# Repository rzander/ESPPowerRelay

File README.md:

# DIY - Smart Home Power Relay (ESP8266)
There exists many Relay-Modules based on ESP8266 or other wireless Modules, but I could not find a Module that fits in a european Wallbox and is independent of protocols or wireless standards. That’s why I've created my own Solution: <br>
<br> 

> **Caution: These modules do not have any certifications… In most countries it’s not legal to use it in Production. <br>And: 230V AC can kill !**

The main goals for this Project are:
 -	As **small** as possible
 -	As **cheap** as possible
 -	As **save** as possible
 -	As **flexible** as possible

Specially the flexibility is something important for me, as I have different scenarios to fulfill and I want to be able to change the wireless technology if it’s required. This is the reason why the result is not a single Module, there are currently 3 Modules: Power, Relay and Wireless (currently based on a ESP8266-12) <br>
 <br>
 <br>
With a **size** of 45mm * 35mm * 20mm (Length, Width, Height) for all three Modules,  it's small enough to mount it in wall (e.g. behind a power switch).

The price for the material is around **14$ (for all three modules)**. 

Eagle and Gerber Files are part of this Project. The Modules are Open-Hardware, feel free to reproduce... Feedback is Welcome.

## Power Module
Input: 100-240V AC<br>
Output: 5V and 3.3V DC (3W Total)<br>
Size: 45mm * 20mm * 20mm (length, width, height)<br>
 <br>

### Schema
 <br>
### Layout
 <br>
### Bill of Materials

|Item|Price (USD)|
|:---|---:|
|1 * Fuse 500ma (MF2410F0.500TM)|0.30|
|1 * Connector Block (4-Ports)|0.70|
|2 * 47uF Tantal Capacitor|0.90|
|1 * Voltage Regulator 3.3V (MC33269ST-3.3T3G)|0.90|
|1 * Power-Supply 5VDC 3W (Hi-Link)|2.75|
|1 * Print|1.00|
|Total:|6.55|

## ESP Module
Size: 40mm * 20mm * 5mm (length, width, height)<br>
<br>

### Schema
 <br>
### Layout
 <br>
### Bill of Materials

|Item|Price (USD)|
|:---|---:|
|4 * Resistor 10k|0.45|
|1 * ESP8266-12F|1.75|
|1 * Print|1.00|
|Total:|3.20|

## Relay Module
Input: PWR 5V, Signal 3V<br>
Output: 250V 10A<br>
Size: 45mm * 10mm * 20mm (length, width, height)<br>
 <br>

### Schema
 <br>

### Layout
 <br>

### Bill of Materials

|Item|Price (USD)|
|:---|---:|
|1 * Gate Driver (MDC3105LT1G)|0.50|
|1 * Relay (ALQ305)|2.35|
|1 * Connector Block (2 Ports)|0.30|
|1 * Print|1.00|
|Total:|4.15|

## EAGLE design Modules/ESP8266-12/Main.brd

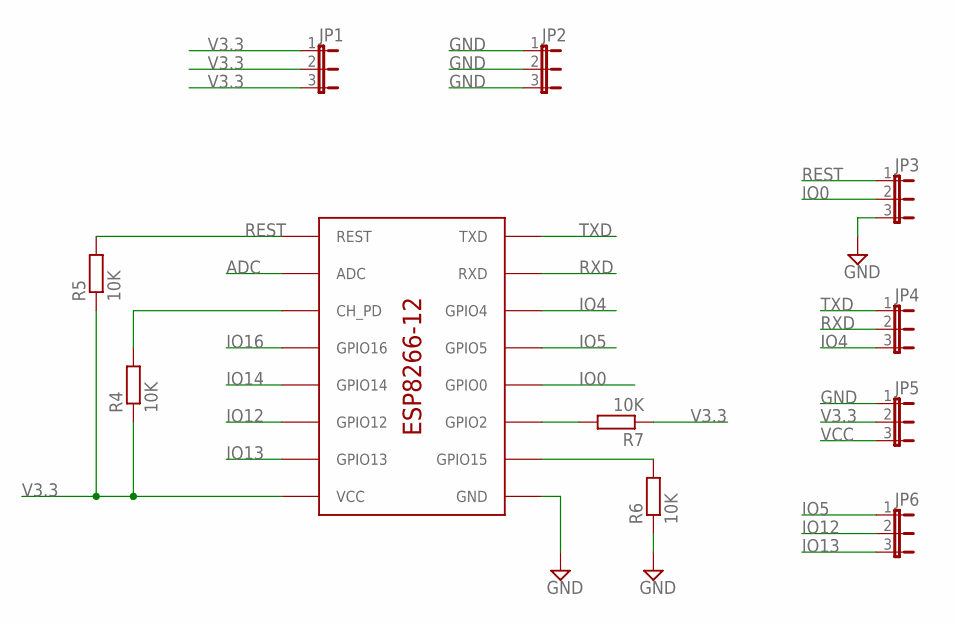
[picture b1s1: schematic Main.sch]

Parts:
JP1, JP2, JP3, JP4, JP5, JP6: JP2E; JP2
R4, R5, R6, R7: 10K; M0805
U$1: ESP8266-12

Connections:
ADC: U$1.ADC
GND: JP2.1, JP2.2, JP2.3, JP3.3, JP5.1, R6.1, U$1.GND
IO0: JP3.2, U$1.GPIO0
IO4: JP4.3, U$1.GPIO4
IO5: JP6.1, U$1.GPIO5
IO12: JP6.2, U$1.GPIO12
IO13: JP6.3, U$1.GPIO13
IO14: U$1.GPIO14
IO16: U$1.GPIO16
unnamed: R4.2, U$1.CH_PD
unnamed: R6.2, U$1.GPIO15
unnamed: R7.2, U$1.GPIO2
REST: JP3.1, R5.2, U$1.REST
RXD: JP4.2, U$1.RXD
TXD: JP4.1, U$1.TXD
V3.3: JP1.1, JP1.2, JP1.3, JP5.2, R4.1, R5.1, R7.1, U$1.VCC
VCC: JP5.3

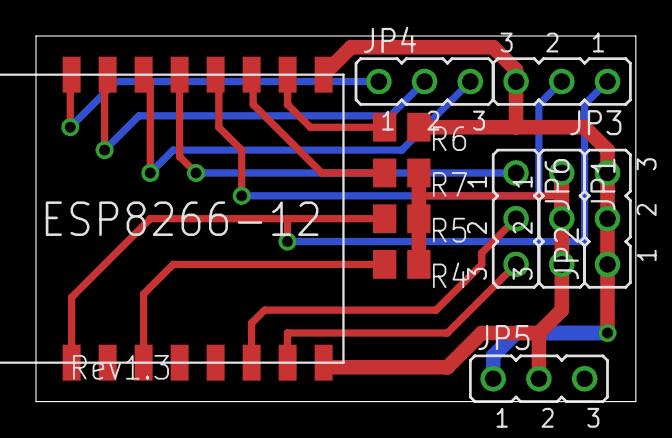
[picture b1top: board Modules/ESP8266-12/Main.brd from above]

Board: 2 copper layers, 33.3 x 20.3 mm, 11 parts (0 on the bottom side), 13 nets.

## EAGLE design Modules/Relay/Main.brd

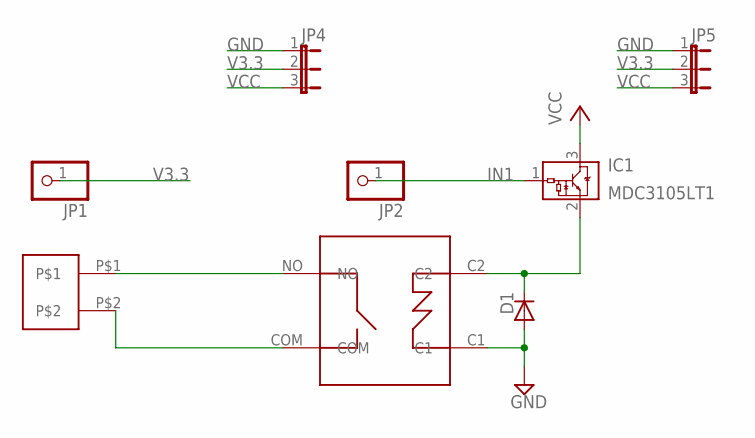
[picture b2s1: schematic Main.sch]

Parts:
D1: DIODE-SOD123; SOD123
IC1: MDC3105LT1; SOT23
JP1, JP2: PINHD-1X1; 1X01
JP4, JP5: JP2E; JP2
REL1: ALQ305
U$2: 1713017

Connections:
GND: D1.A, JP4.1, JP5.1, REL1.C1
IN1: IC1.1 (VIN), JP2.1
unnamed: D1.C, IC1.2 (GND), REL1.C2
P$1: REL1.NO, U$2.P$1
P$2: REL1.COM, U$2.P$2
V3.3: JP1.1, JP4.2, JP5.2
VCC: IC1.3 (VOUT), JP4.3, JP5.3

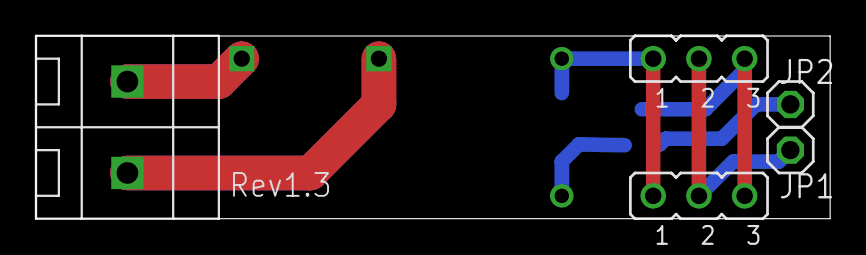
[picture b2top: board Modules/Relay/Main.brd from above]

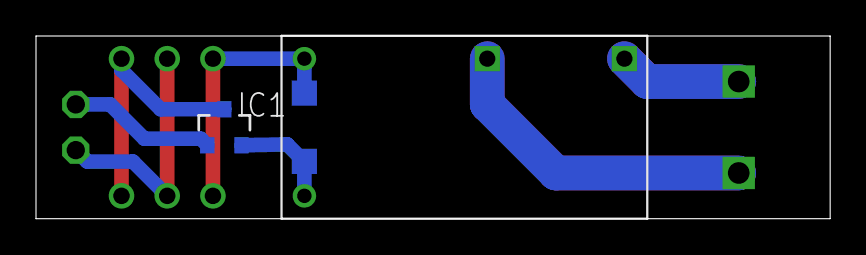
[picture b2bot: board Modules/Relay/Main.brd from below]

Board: 2 copper layers, 44.1 x 10.2 mm, 8 parts (3 on the bottom side), 7 nets.

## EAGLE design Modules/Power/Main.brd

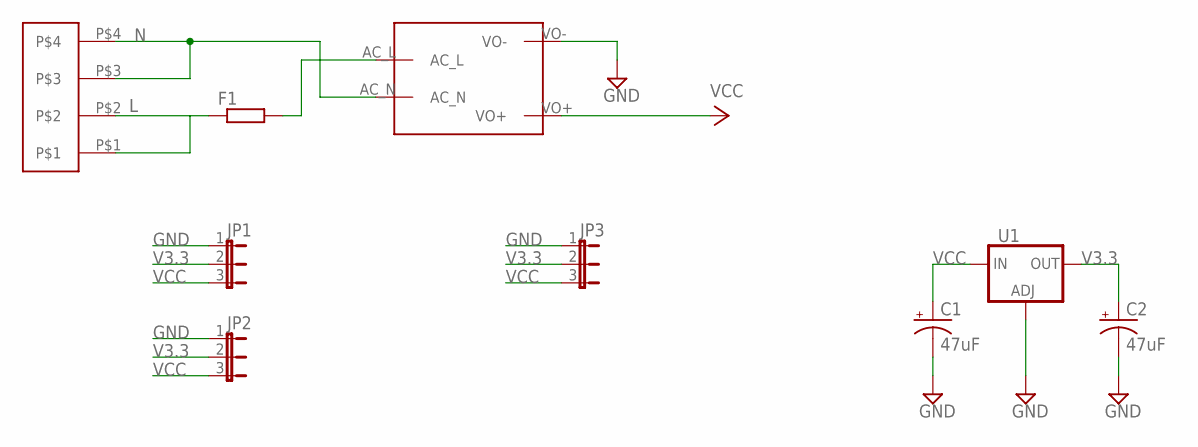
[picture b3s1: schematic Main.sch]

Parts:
17928891: 1792889
C1, C2: 47uF; EIA3528
F1: R-EU_R2010W; R2010W
JP1, JP2, JP3: JP2E; JP2
PWR1: MAINS_CONVERTERS; HLK-PM01
U1: V_REG_3.3V; SOT223

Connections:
GND: C1.C (-), C2.C (-), JP1.1, JP2.1, JP3.1, PWR1.VO-, U1.1 (ADJ)
L: 17928891.P$1, 17928891.P$2, F1.1
N: 17928891.P$3, 17928891.P$4, PWR1.AC_N
unnamed: F1.2, PWR1.AC_L
V3.3: C2.A (+), JP1.2, JP2.2, JP3.2, U1.2 (OUT)
VCC: C1.A (+), JP1.3, JP2.3, JP3.3, PWR1.VO+, U1.3 (IN)

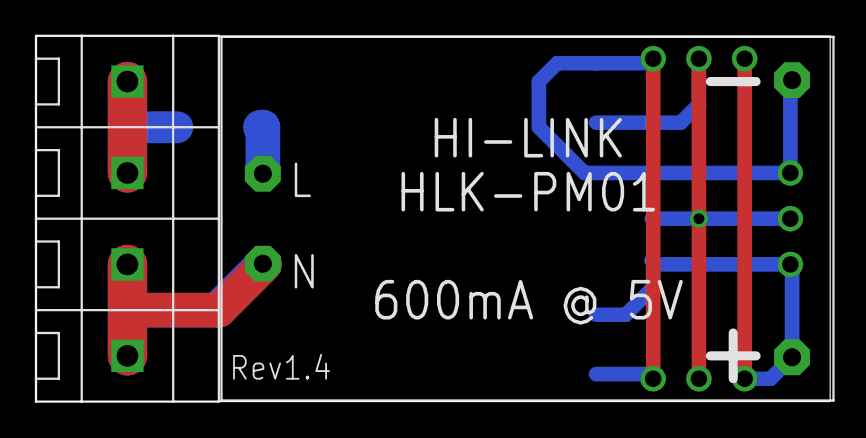
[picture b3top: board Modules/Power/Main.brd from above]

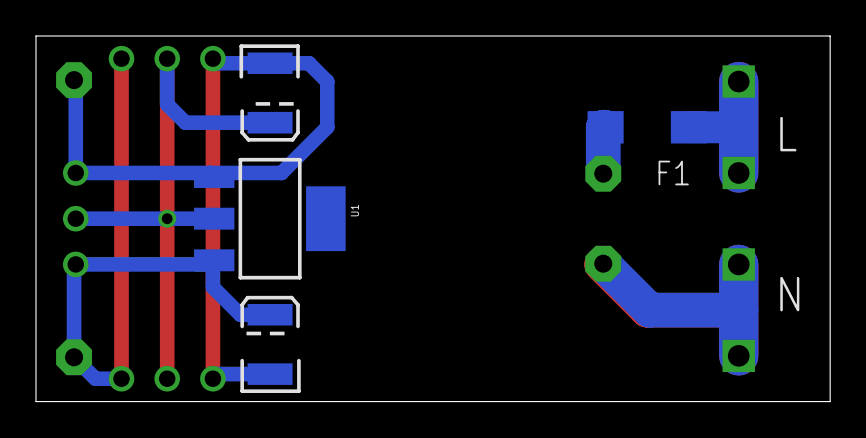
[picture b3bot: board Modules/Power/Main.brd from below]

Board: 2 copper layers, 44.1 x 20.3 mm, 9 parts (4 on the bottom side), 6 nets.

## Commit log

2016-09-12 Initial upload

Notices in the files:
parts and their libraries:
SparkFun-Capacitors: Licensing: CC v3.0 Share-Alike You are welcome to use this library for commercial purposes.
